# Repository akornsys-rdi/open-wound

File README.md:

# open-wound #

                                                      _ 
         ___ _ __  ___ _ _   __ __ _____ _  _ _ _  __| |
        / _ \ '_ \/ -_) ' \  \ V  V / _ \ || | ' \/ _` |
        \___/ .__/\___|_||_|  \_/\_/\___/\_,_|_||_\__,_|
            |_|                                         

open wound, the system behind the [CUT artwork](http://arturomoyavillen.com/cut).

## ChangeLog  ##

-   Cambios generales:  
    *   Ahora open wound está bajo licencia GPLv3.  
    *   Open wound usa [versionamiento semántico](http://semver.org).  
-   Esclavos version 1.0.0:  
    *   Cambios menores en PCB.  
    *   El microcontrolador pasa a ser parte de la placa, no un módulo Arduino.  
    *   Los pines sin usar son salidas a nivel bajo no conectadas en lugar de entradas a masa.  
    *   Se añade un conector AVRISP de seis pines.  
    *   Se añade un conector de debug.  
    *   Placa diseñada en SMT..  
    *   Mejorado el método de conexión a la plancha sensora.  
    *   Ahora se usan conectores subminiatura con enclavamiento para su conexión.  
-   Maestro en versión 1.0.0-alpha:  
    *   El maestro ahora dispone de catorce canales para esclavos.  
    *   Se permiten cuatro canales para PIR compatibles con los esclavos.  
    *   Cambiado el CI amplificador.  
    *   Entrada de audio compacta medianteconector DA15F.  
    *   Buffer digital trigger-schmitt para acondicionar la señar de los esclavos.  
    *   Usa los propios LED del RJ45 para indicar conexión y dato entrante.  
    *   Ahora usa [FreeCanvas](https://github.com/synusia/freecanvas).

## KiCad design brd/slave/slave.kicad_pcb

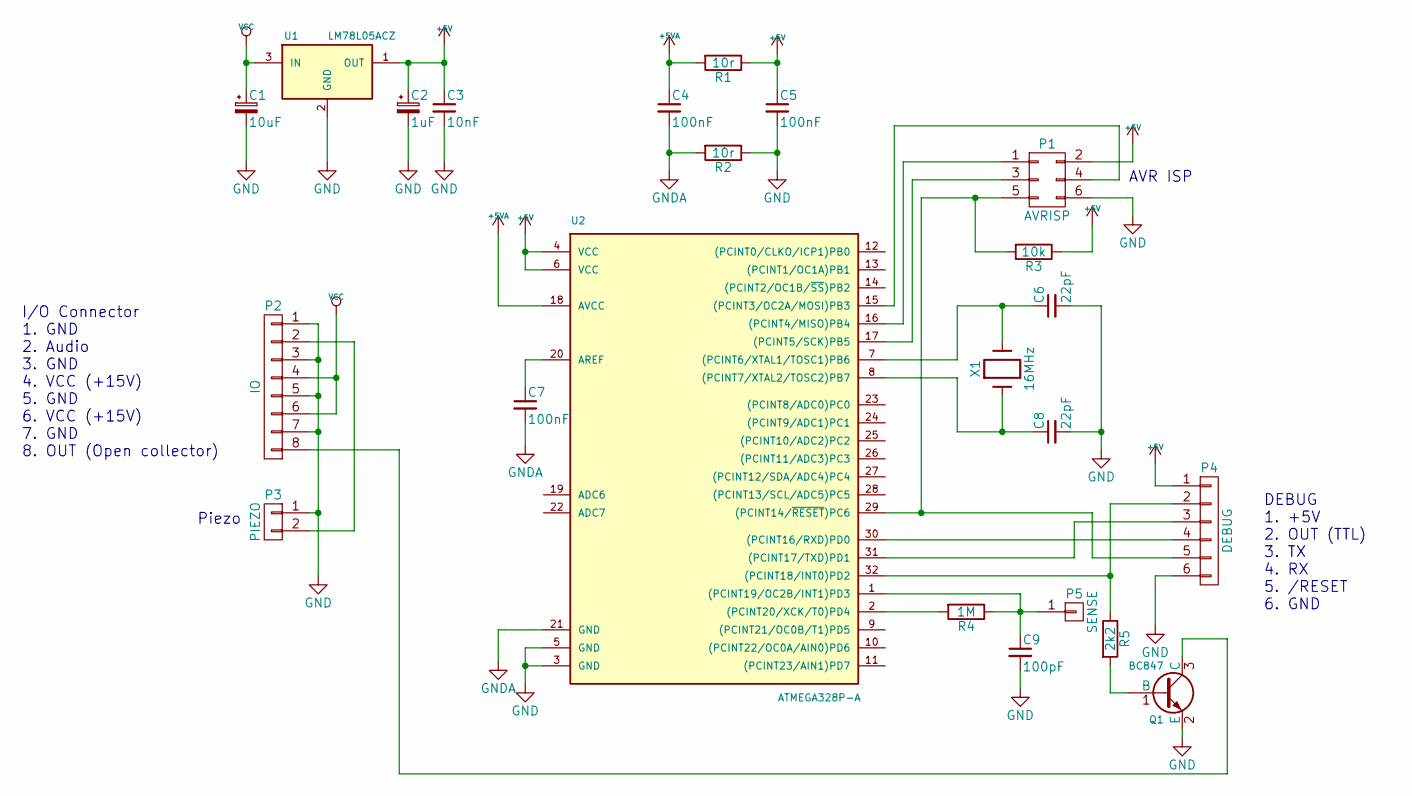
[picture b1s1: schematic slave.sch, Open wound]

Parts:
C1: 10uF; c_elec_5x5.3
C2: 1uF; c_elec_4x5.3
C3: 10nF; C_0603_HandSoldering
C4, C5, C7: 100nF; C_0603_HandSoldering
C6, C8: 22pF; C_0603_HandSoldering
C9: 100pF; C_0603_HandSoldering
P1: AVRISP; Pin_Header_Straight_2x03
P2: IO; IL-Z-8PL-SMTYE
P3: PIEZO; IL-Z-2PL-SMTYE
P4: DEBUG; IL-Z-6PL-SMTYE
P5: SENSE; SolderWirePad_single_2mmDrill
Q1: BC847; SOT-23_Handsoldering
R1, R2: 10r; R_0603_HandSoldering
R3: 10k; R_0805_HandSoldering
R4: 1M; R_0805_HandSoldering
R5: 2k2; R_0805_HandSoldering
U1: LM78L05ACZ; SOT89-3_Housing_Handsoldering
U2: ATMEGA328P-A; TQFP-32_7x7mm_Pitch0.8mm
X1: 16MHz; Q_49U3HMS

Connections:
+5V: C2.1, C3.1, C5.1, P1.2, P4.1, R1.1, R3.1, U1.1 (OUT), U2.4 (VCC), U2.6 (VCC)
+5VA: C4.1, R1.2, U2.18 (AVCC)
GND: C1.2, C2.2, C3.2, C5.2, C6.2, C8.2, C9.2, P1.6, P2.1, P2.3, P2.5, P2.7, P3.1, P4.6, Q1.2 (E), R2.1, U1.2 (GND), U2.3 (GND), U2.5 (GND)
GNDA: C4.2, C7.2, R2.2, U2.21 (GND)
unnamed: C6.1, U2.7 ((PCINT6/XTAL1/TOSC1)PB6), X1.2
unnamed: C7.1, U2.20 (AREF)
unnamed: C8.1, U2.8 ((PCINT7/XTAL2/TOSC2)PB7), X1.1
unnamed: C9.1, P5.1, R4.1, U2.1 ((PCINT19/OC2B/INT1)PD3)
unnamed: P1.1, U2.16 ((PCINT4/MISO)PB4)
unnamed: P1.3, U2.17 ((PCINT5/SCK)PB5)
unnamed: P1.4, U2.15 ((PCINT3/OC2A/MOSI)PB3)
unnamed: P1.5, P4.5, R3.2, U2.29 ((PCINT14/~RESET~)PC6)
unnamed: P2.2, P3.2
unnamed: P2.8, Q1.3 (C)
unnamed: P4.2, R5.1, U2.32 ((PCINT18/INT0)PD2)
unnamed: P4.3, U2.31 ((PCINT17/TXD)PD1)
unnamed: P4.4, U2.30 ((PCINT16/RXD)PD0)
unnamed: Q1.1 (B), R5.2
unnamed: R4.2, U2.2 ((PCINT20/XCK/T0)PD4)
VCC: C1.1, P2.4, P2.6, U1.3 (IN)

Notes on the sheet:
Piezo
AVR ISP
DEBUG 1. +5V 2. OUT (TTL) 3. TX 4. RX 5. /RESET 6. GND
I/O Connector 1. GND 2. Audio 3. GND 4. VCC (+15V) 5. GND 6. VCC (+15V) 7. GND 8. OUT (Open collector)

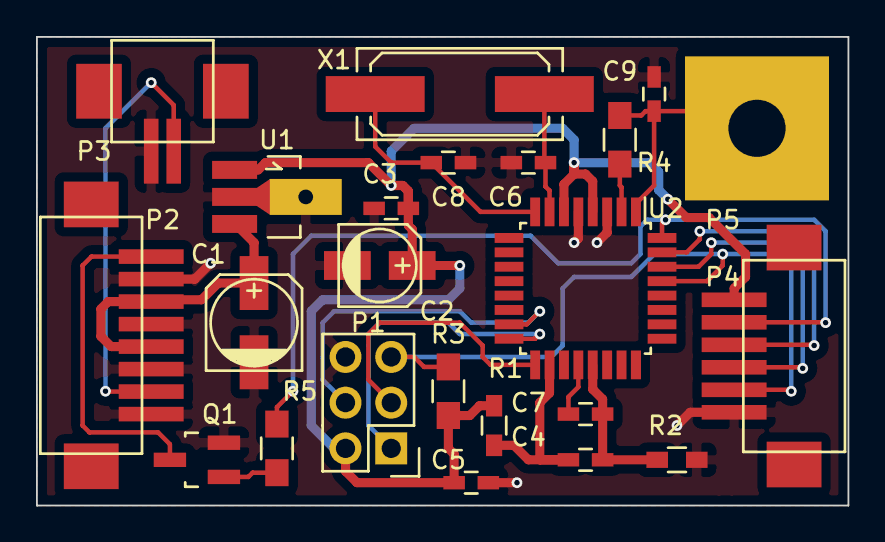
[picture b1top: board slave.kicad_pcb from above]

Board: 2 copper layers, 45.1 x 26.0 mm, 23 parts (0 on the bottom side), 20 nets.

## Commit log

2014-06-03 upload files
2014-06-21 updated out files
2014-07-30 new rc2 version
2014-07-31 tab align issues
2014-08-01 master rc2 version
2014-08-01 added changelog to readme
2014-12-15 layout rework & gerber generation for slave pcb
2015-05-24 slave version rc3
2015-06-24 master rc3 w/ freecanvas alpha
2015-06-30 actualizada galería
2015-06-30 modificada licencia a GPLv3
2015-06-30 versión 1.0.0
2015-06-30 corregido descripción en archivos del maestro
2015-06-30 añadidos BOM de mouser
2015-08-31 versión slave 1.0.1 añadido BOM y referencias a esquemático
2017-03-20 update README.md with new URL

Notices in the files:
brd/slave/slave.kicad_pcb:
Under MIT License
UNDER GPLv3 LICENSE
